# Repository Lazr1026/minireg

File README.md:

## Minireg
Minireg is a voltage regulator for the Wii U, supporting 1S lithium battery setups or 3v-5v input from a power supply.
It is based of YveltalGriffins bistro regulator board which you can find [here](https://github.com/mackieks/bistro).

It is intended to be used with the WUP-50, however it should also work on the previous board revisions (WUP-01 to WUP-40).

[BOM](https://www.mouser.com/ProjectManager/ProjectDetail.aspx?AccessID=c76b1d7a55)

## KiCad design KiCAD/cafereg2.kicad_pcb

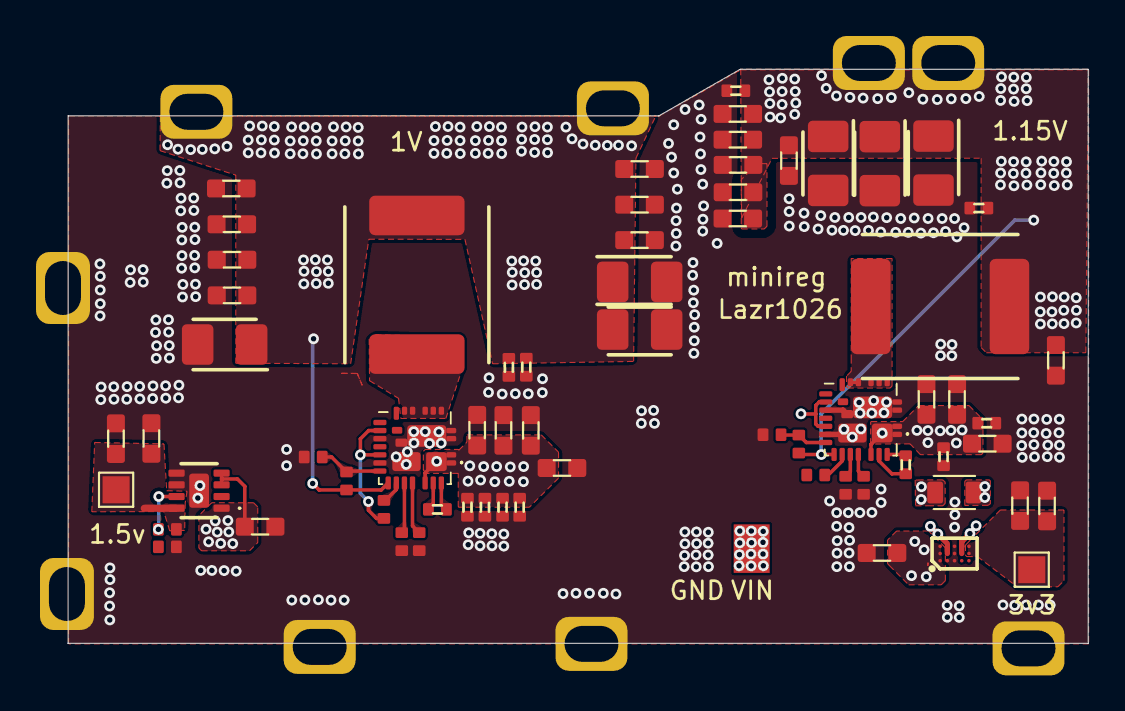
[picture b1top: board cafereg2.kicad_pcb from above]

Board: 4 copper layers, 56.7 x 31.9 mm, 66 parts (0 on the bottom side), 23 nets.

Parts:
3v3, 3v3#2: TestPoint_Pad_1.5x1.5mm
C1, C2, C3, C9, C10, C11, C12, C13, C14, C15, C20, C21, C22, C28, C29, C30, C31, C32, C33, C34, C39, C39#2, C40, C41, C42, C43, C44: 22uF; C0603
C4, C7, C8, C16, C23, C26, C27, C35: 0.1uF; C0402
C5, C24: 1uF; C0402
C6, C25: 2.2uF; C0402
C17, C18, C19, C36, C37, C38: F930J107KBA; CAPPM3528X210N
IC1, IC2: SiC431CED-T1-GE3; SIC431AEDT1GE3
IC3: TPS63810YFFR; BGA15C40P3X5_134X226X62
IC4: MUN3CAD03-SE; MUN3CAD03SE
L1, L2: MPXV1D0840L1R0; INDPM8680X400N
L3: TFM201208BLE-R47MTCF; INDC2009X120
R1, R6: 100k; R0402
R2, R3, R7, R8: 510k; R0402
R4: 6.67k; R0402
R5: 10K; R0402
R9: 11k; R0402
R10: 12k; R0402
R11: 200k; R0402
R12: 133k; R0402

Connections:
/MUN3CAD03-SE 1.5V 3A/1.5V: C43.1, C44.1, IC4.8 (VOUT), R11.2
/SiC431 1V 20A/1V: C8.2, C9.1, C10.1, C11.1, C12.1, C13.1, C14.1, C15.1, C16.1, C17.1 (+), C18.1 (+), C19.1 (+), IC1.18 (VOUT), L1.2, R4.2
/SiC438 1.15V 8A/1.15V: C27.2, C28.1, C29.1, C30.1, C31.1, C32.1, C33.1, C34.1, C35.1, C36.1 (+), C37.1 (+), C38.1 (+), IC2.18 (VOUT), L2.2, R9.2
/TPS63810 3.3V 2.5A/3.3V: 3v3#2.1, C40.1, C41.1, IC3.E2 (VOUT_1), IC3.E3 (VOUT_2)
GND: C1.2, C2.2, C3.2, C4.2, C5.2, C6.2, C8.1, C9.2, C10.2, C11.2, C12.2, C13.2, C14.2, C15.2, C16.2, C17.2 (-), C18.2 (-), C19.2 (-), C20.2, C21.2, C22.2, C23.2, C24.2, C25.2, C27.1, C28.2, C29.2, C30.2, C31.2, C32.2, C33.2, C34.2, C35.2, C36.2 (-), C37.2 (-), C38.2 (-), C39.2, C39#2.2, C40.2, C41.2, C42.2, C43.2, C44.2, IC1.3 (PGND_1), IC1.4 (PGND_2), IC1.13 (PGND_3), IC1.16 (AGND_1), IC1.25 (AGND_2), IC1.27 (PGND_4), IC1.29 (PGND_1), IC2.3 (PGND_1), IC2.4 (PGND_2), IC2.13 (PGND_3), IC2.16 (AGND_1), IC2.25 (AGND_2), IC2.27 (PGND_4), IC2.29 (PGND_1), IC3.B1 (VSEL), IC3.C1 (AGND), IC3.C2 (GND_1), IC3.C3 (GND_2), IC4.5 (GND_1), IC4.6 (GND_2), IC4.9 (GND_3), R2.1, R3.1, R5.1, R7.1, R8.1, R10.1, R12.1
unnamed: C7.1, IC1.23 (BOOT)
unnamed: IC1.19 (EN), R1.1
unnamed: IC1.17 (FB), R4.1, R5.2
unnamed: IC1.21 (MODE1), R2.2
unnamed: IC1.20 (MODE2), R3.2
unnamed: C7.2, IC1.24 (PHASE)
unnamed: IC1.5 (SW_1), IC1.6 (SW_2), IC1.7 (SW_3), IC1.8 (SW_4), IC1.9 (SW_5), L1.1
unnamed: C26.1, IC2.23 (BOOT)
unnamed: IC2.19 (EN), R6.1
unnamed: IC2.17 (FB), R9.1, R10.2
unnamed: IC2.21 (MODE1), R7.2
unnamed: IC2.20 (MODE2), R8.2
unnamed: C26.2, IC2.24 (PHASE)
unnamed: IC2.5 (SW_1), IC2.6 (SW_2), IC2.7 (SW_3), IC2.8 (SW_4), IC2.9 (SW_5), L2.1
unnamed: IC3.B2 (LX1_1), IC3.B3 (LX1_2), L3.1
unnamed: IC3.D2 (LX2_1), IC3.D3 (LX2_2), L3.2
unnamed: IC4.7 (FB), R11.1, R12.2
VIN: 3v3.1, C1.1, C2.1, C3.1, C4.1, C5.1, C6.1, C20.1, C21.1, C22.1, C23.1, C24.1, C25.1, C39.1, C39#2.1, C42.1, IC1.1 (VIN_1), IC1.2 (VIN_2), IC1.12 (VDRV), IC1.15 (VDD), IC1.22 (VIN_3), IC1.26 (VIN_4), IC2.1 (VIN_1), IC2.2 (VIN_2), IC2.12 (VDRV), IC2.15 (VDD), IC2.22 (VIN_3), IC2.26 (VIN_4), IC3.A1 (EN), IC3.A2 (VIN_1), IC3.A3 (VIN_2), IC4.1 (EN), IC4.3 (VIN_1), IC4.4 (VIN_2), R1.2, R6.2

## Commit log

2024-07-28 Fix problems with the PCB
2024-07-28 Add jig and my name to the silkscreen
2024-07-28 Add BOM to readme
